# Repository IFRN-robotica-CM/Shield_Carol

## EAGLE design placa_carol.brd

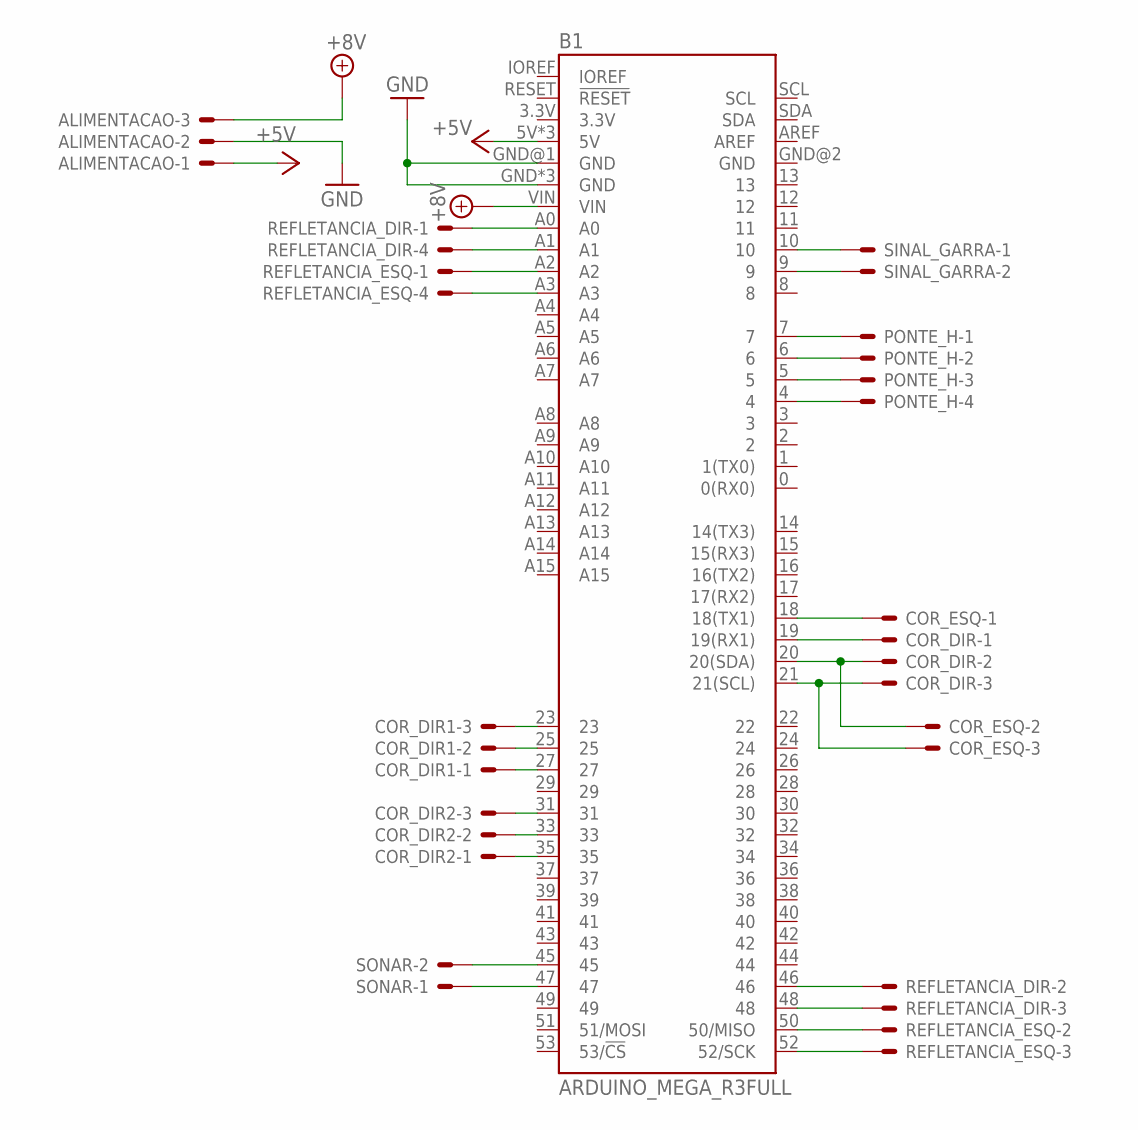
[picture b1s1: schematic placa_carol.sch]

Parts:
ALIMENTACAO: KK-156-3
B1: ARDUINO_MEGA_R3FULL; ARDUINO_MEGA_NO_SILK
COR_DIR, COR_DIR1, COR_DIR2: JST-XH-03-PIN-LONG-PAD; JST-XH-03-PACKAGE-LONG-PAD
COR_ESQ: JST-XH-03-PIN-LONG-PAD; JST-XH-03-PACKAGE-LONG-PAD
PONTE_H: JST-XH-04-PIN-LONG-PAD; JST-XH-04-PACKAGE-LONG-PAD
REFLETANCIA_DIR: JST-XH-04-PIN-LONG-PAD; JST-XH-04-PACKAGE-LONG-PAD
REFLETANCIA_ESQ: JST-XH-04-PIN-LONG-PAD; JST-XH-04-PACKAGE-LONG-PAD
SINAL_GARRA: JST-XH-02-PIN-LONG-PAD; JST-XH-02-PACKAGE-LONG-PAD
SONAR: JST-XH-02-PIN-LONG-PAD; JST-XH-02-PACKAGE-LONG-PAD

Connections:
+5V: ALIMENTACAO.1, B1.5V, B1.5V@1 (5V), B1.5V@2 (5V)
+8V: ALIMENTACAO.3, B1.VIN
GND: ALIMENTACAO.2, B1.GND, B1.GND@1 (GND), B1.GND@3 (GND), B1.GND@4 (GND)
unnamed: B1.7, PONTE_H.1
unnamed: B1.6, PONTE_H.2
unnamed: B1.5, PONTE_H.3
unnamed: B1.4, PONTE_H.4
unnamed: B1.19 (19(RX1)), COR_DIR.1
unnamed: B1.20 (20(SDA)), COR_DIR.2, COR_ESQ.2
unnamed: B1.18 (18(TX1)), COR_ESQ.1
unnamed: B1.45, SONAR.2
unnamed: B1.21 (21(SCL)), COR_DIR.3, COR_ESQ.3
unnamed: B1.47, SONAR.1
unnamed: B1.A0, REFLETANCIA_DIR.1
unnamed: B1.A1, REFLETANCIA_DIR.4
unnamed: B1.A2, REFLETANCIA_ESQ.1
unnamed: B1.A3, REFLETANCIA_ESQ.4
unnamed: B1.46, REFLETANCIA_DIR.2
unnamed: B1.48, REFLETANCIA_DIR.3
unnamed: B1.50 (50/MISO), REFLETANCIA_ESQ.2
unnamed: B1.52 (52/SCK), REFLETANCIA_ESQ.3
unnamed: B1.27, COR_DIR1.1
unnamed: B1.25, COR_DIR1.2
unnamed: B1.10, SINAL_GARRA.1
unnamed: B1.9, SINAL_GARRA.2
unnamed: B1.23, COR_DIR1.3
unnamed: B1.31, COR_DIR2.3
unnamed: B1.33, COR_DIR2.2
unnamed: B1.35, COR_DIR2.1

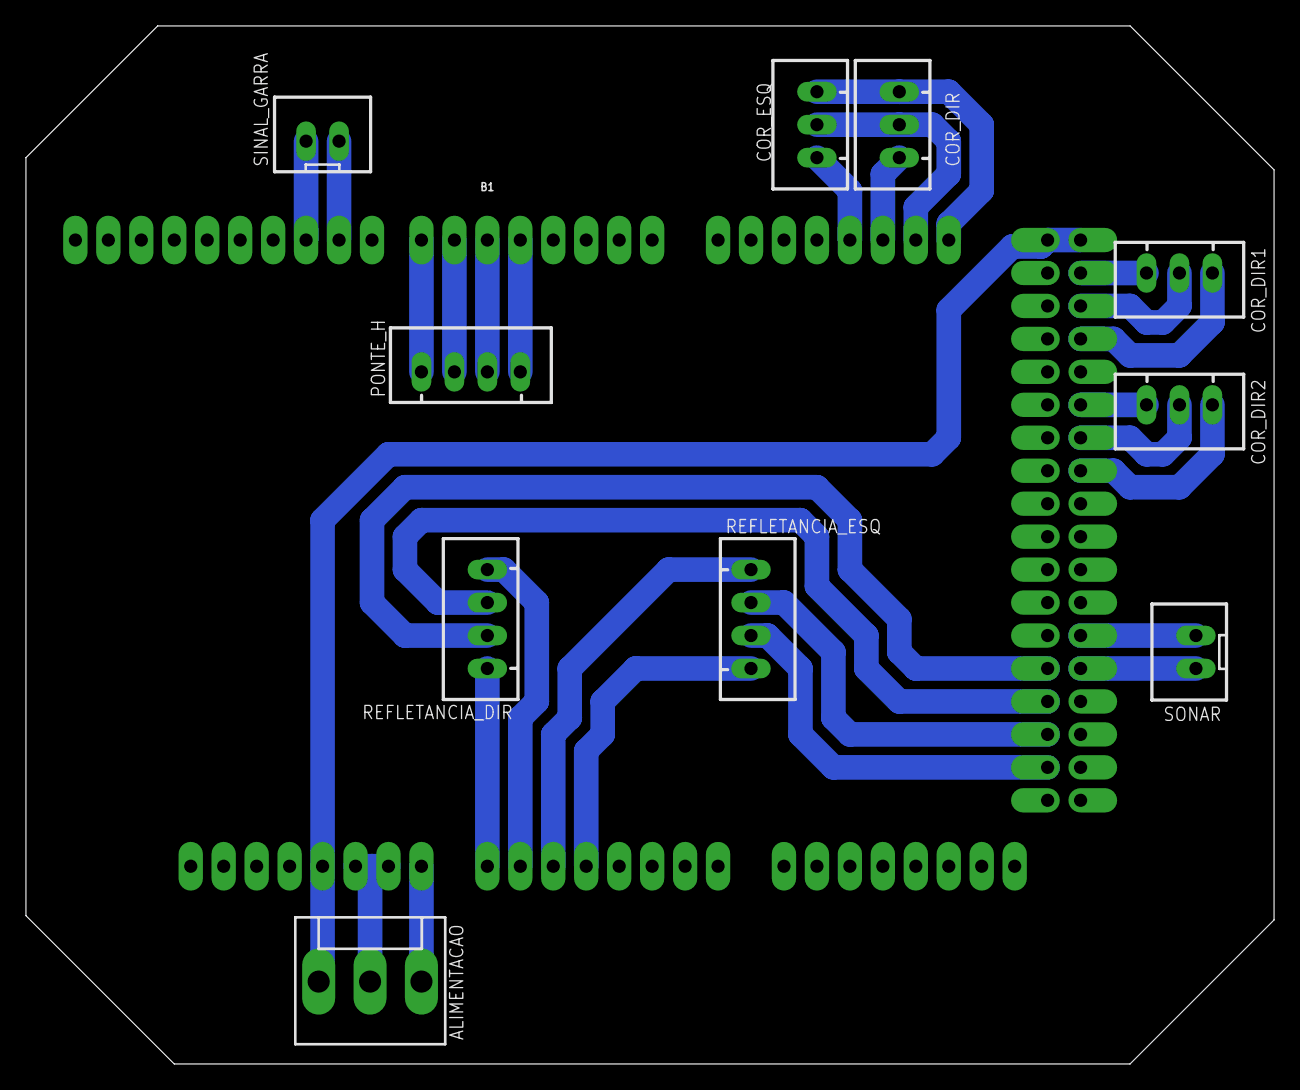
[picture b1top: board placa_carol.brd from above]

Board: 2 copper layers, 96.2 x 80.0 mm, 11 parts (0 on the bottom side), 29 nets.

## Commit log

2024-02-22 Arquivos das placas adicionados
2024-02-22 arquivos ignorados

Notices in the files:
parts and their libraries:
SparkFun-Boards: Licensing: Creative Commons ShareAlike 4.0 International - https://creativecommons.org/licenses/by-sa/4.0
